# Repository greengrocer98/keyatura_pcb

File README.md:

# KEYATURA
Keyatura (/ˌkeɪ.əˈtʊə.rə/) - 36-key ergonomic keyboard with MX-spacing and support of choc_v2v1/MX switches.

### Features
* Promicro compatible MCU
* Hotswap for choc/MX
* Three led indicators
* Mill-Max hotswap sockets for MCU
* Power switch
* Reset button
### PCB
#### <div align="center">Top<div>

#### <div align="center">Bottom<div>

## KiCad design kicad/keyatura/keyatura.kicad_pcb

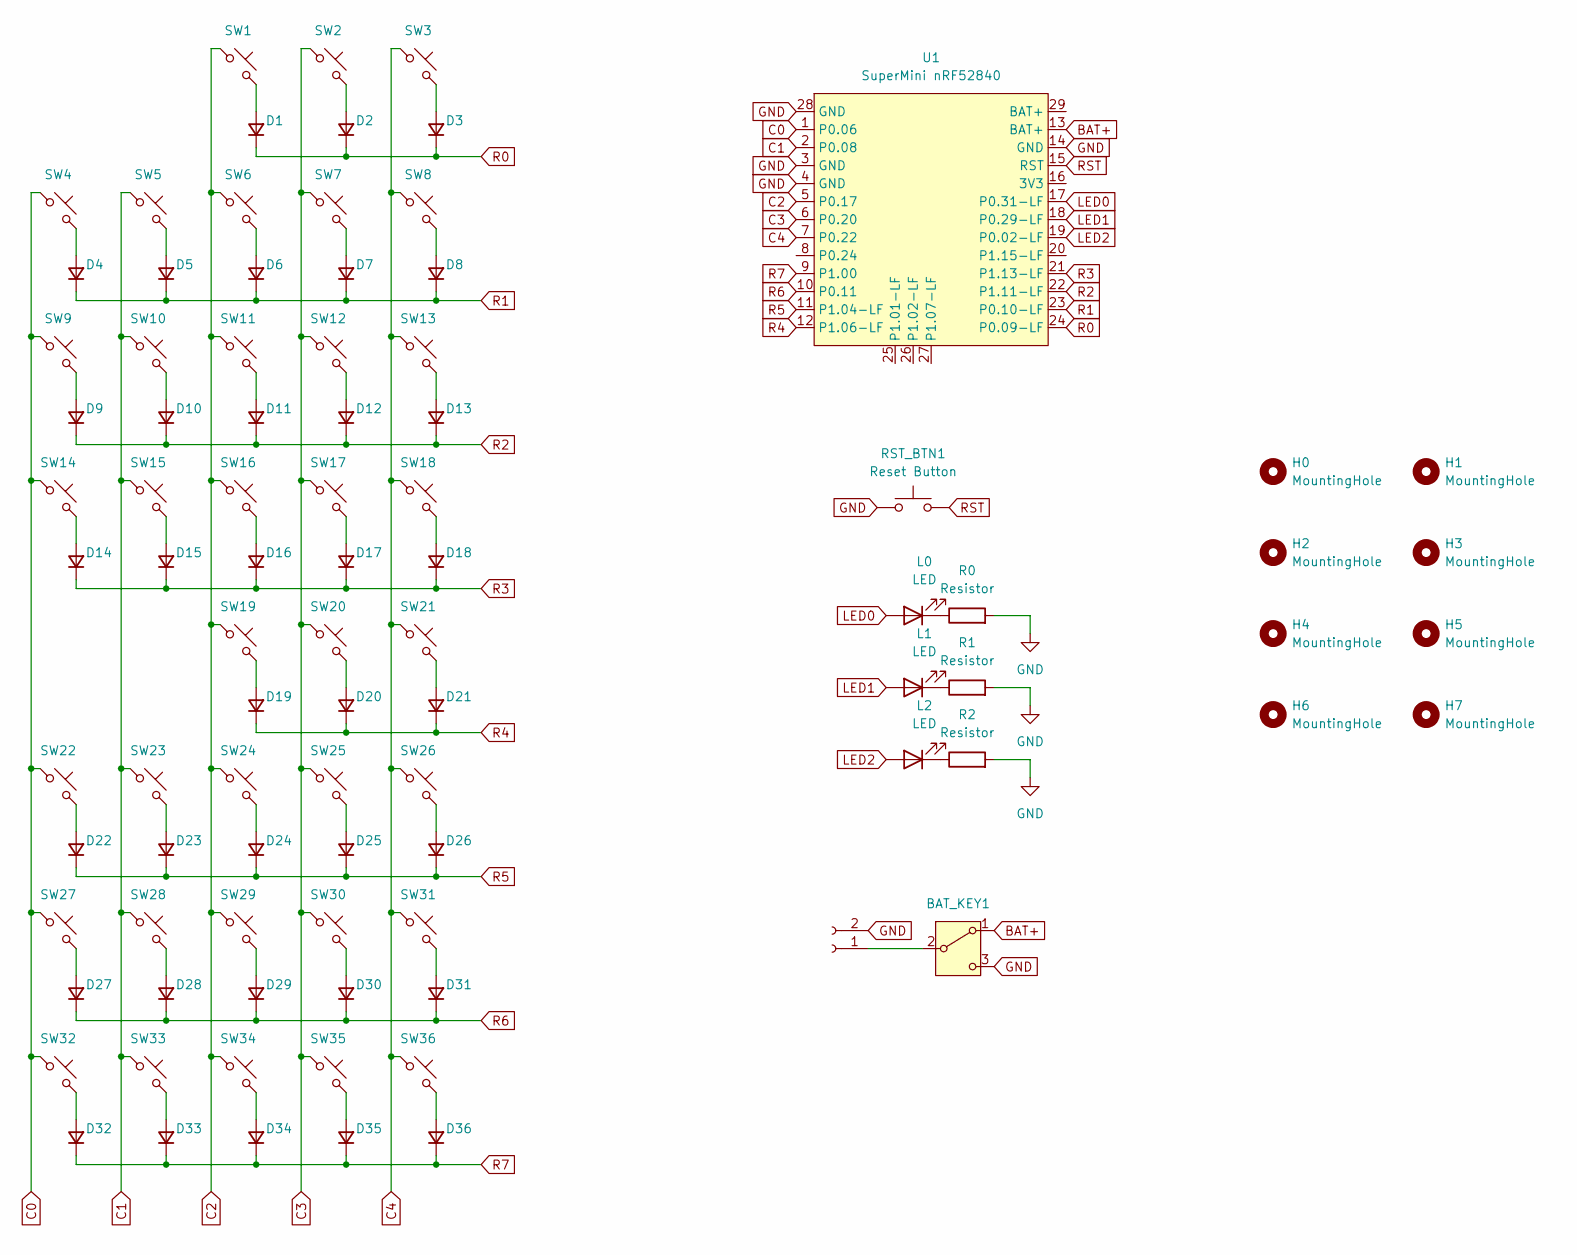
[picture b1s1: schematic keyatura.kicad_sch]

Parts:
BAT_KEY1: SW_SPDT; MSK-12C02
D1, D2, D3, D4, D5, D6, D7, D8, D9, D10, D11, D12, D13, D14, D15, D16, D17, D18, D19, D20, D21, D22, D23, D24, D25, D26, D27, D28, D29, D30, D31, D32, D33, D34, D35, D36: D; diode
H0, H1, H2, H3, H4, H5, H6, H7: MountingHole; mounting hole
J1: Battery; battery
L0, L1, L2: LED
R0, R1, R2: Resistor; resistor
RST_BTN1: Reset Button; reset button
SW1, SW2, SW3, SW4, SW5, SW6, SW7, SW8, SW9, SW10, SW11, SW12, SW13, SW14, SW15, SW16, SW17, SW18, SW19, SW20, SW21, SW22, SW23, SW24, SW25, SW26, SW27, SW28, SW29, SW30, SW31, SW32, SW33, SW34, SW35, SW36: SW_Push; SW_MX_Kailh_Choc_V1V2_HotSwap_Hybrid
U1: SuperMini nRF52840; supermini

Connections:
BAT+: BAT_KEY1.1 (A), U1.13 (BAT+)
C0: SW4.1, SW9.1, SW14.1, SW22.1, SW27.1, SW32.1, U1.1 (P0.06)
C1: SW5.1, SW10.1, SW15.1, SW23.1, SW28.1, SW33.1, U1.2 (P0.08)
C2: SW1.1, SW6.1, SW11.1, SW16.1, SW19.1, SW24.1, SW29.1, SW34.1, U1.5 (P0.17)
C3: SW2.1, SW7.1, SW12.1, SW17.1, SW20.1, SW25.1, SW30.1, SW35.1, U1.6 (P0.20)
C4: SW3.1, SW8.1, SW13.1, SW18.1, SW21.1, SW26.1, SW31.1, SW36.1, U1.7 (P0.22)
GND: BAT_KEY1.3 (C), J1.2, R0.2, R1.2, R2.2, RST_BTN1.1, U1.3 (GND), U1.4 (GND), U1.14 (GND), U1.28 (GND)
LED0: L0.2 (A), U1.17 (P0.31-LF)
LED1: L1.2 (A), U1.18 (P0.29-LF)
LED2: L2.2 (A), U1.19 (P0.02-LF)
unnamed: BAT_KEY1.2 (B), J1.1
unnamed: D1.2 (A), SW1.2
unnamed: D2.2 (A), SW2.2
unnamed: D3.2 (A), SW3.2
unnamed: D4.2 (A), SW4.2
unnamed: D5.2 (A), SW5.2
unnamed: D6.2 (A), SW6.2
unnamed: D7.2 (A), SW7.2
unnamed: D8.2 (A), SW8.2
unnamed: D9.2 (A), SW9.2
unnamed: D10.2 (A), SW10.2
unnamed: D11.2 (A), SW11.2
unnamed: D12.2 (A), SW12.2
unnamed: D13.2 (A), SW13.2
unnamed: D14.2 (A), SW14.2
unnamed: D15.2 (A), SW15.2
unnamed: D16.2 (A), SW16.2
unnamed: D17.2 (A), SW17.2
unnamed: D18.2 (A), SW18.2
unnamed: D19.2 (A), SW19.2
unnamed: D20.2 (A), SW20.2
unnamed: D21.2 (A), SW21.2
unnamed: D22.2 (A), SW22.2
unnamed: D23.2 (A), SW23.2
unnamed: D24.2 (A), SW24.2
unnamed: D25.2 (A), SW25.2
unnamed: D26.2 (A), SW26.2
unnamed: D27.2 (A), SW27.2
unnamed: D28.2 (A), SW28.2
unnamed: D29.2 (A), SW29.2
unnamed: D30.2 (A), SW30.2
unnamed: D31.2 (A), SW31.2
unnamed: D32.2 (A), SW32.2
unnamed: D33.2 (A), SW33.2
unnamed: D34.2 (A), SW34.2
unnamed: D35.2 (A), SW35.2
unnamed: D36.2 (A), SW36.2
unnamed: L0.1 (K), R0.1
unnamed: L1.1 (K), R1.1
unnamed: L2.1 (K), R2.1
R0: D1.1 (K), D2.1 (K), D3.1 (K), U1.24 (P0.09-LF)
R1: D4.1 (K), D5.1 (K), D6.1 (K), D7.1 (K), D8.1 (K), U1.23 (P0.10-LF)
R2: D9.1 (K), D10.1 (K), D11.1 (K), D12.1 (K), D13.1 (K), U1.22 (P1.11-LF)
R3: D14.1 (K), D15.1 (K), D16.1 (K), D17.1 (K), D18.1 (K), U1.21 (P1.13-LF)
R4: D19.1 (K), D20.1 (K), D21.1 (K), U1.12 (P1.06-LF)
R5: D22.1 (K), D23.1 (K), D24.1 (K), D25.1 (K), D26.1 (K), U1.11 (P1.04-LF)
R6: D27.1 (K), D28.1 (K), D29.1 (K), D30.1 (K), D31.1 (K), U1.10 (P0.11)
R7: D32.1 (K), D33.1 (K), D34.1 (K), D35.1 (K), D36.1 (K), U1.9 (P1.00)
RST: RST_BTN1.2, U1.15 (RST)

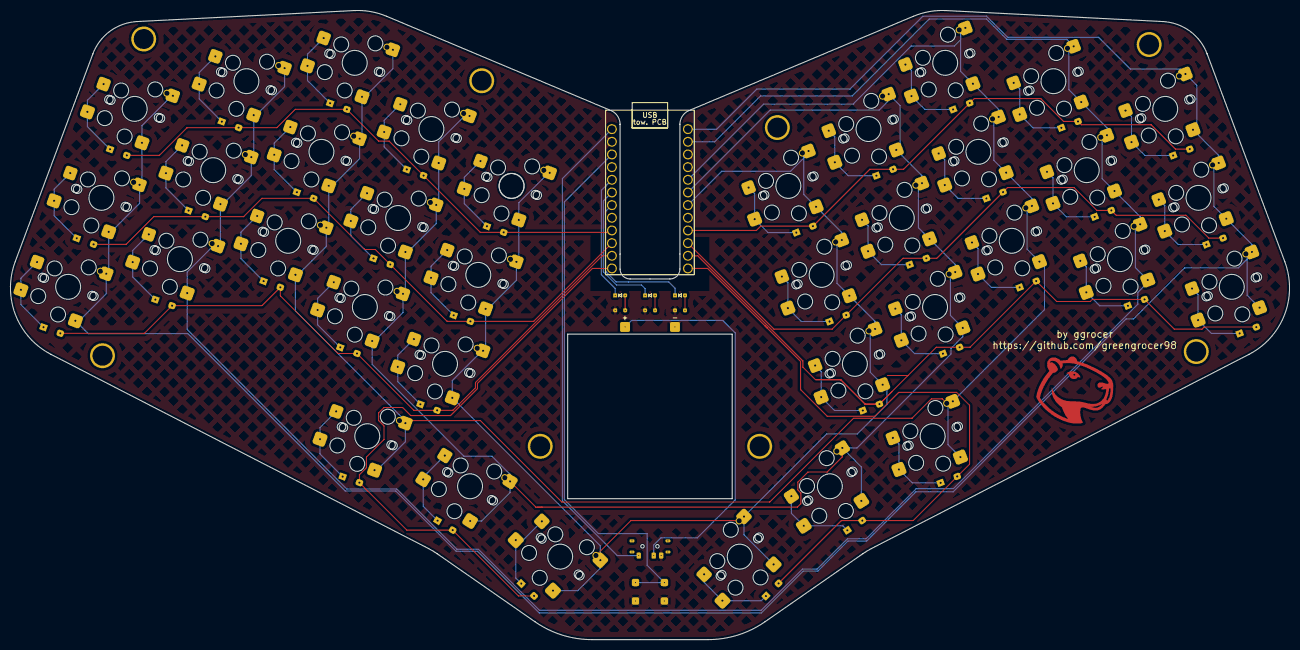
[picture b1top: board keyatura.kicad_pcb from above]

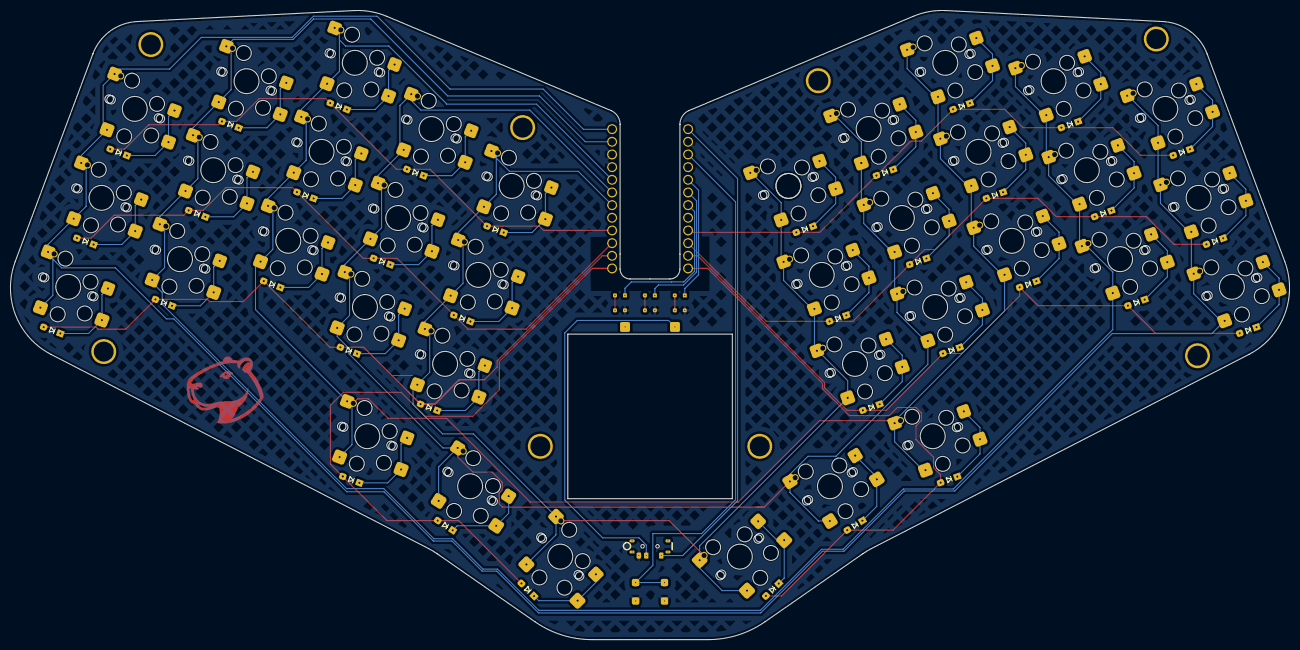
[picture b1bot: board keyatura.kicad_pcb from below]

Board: 2 copper layers, 256.5 x 126.2 mm, 90 parts (37 on the bottom side), 59 nets.

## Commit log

2025-08-06 initial work
2025-08-06 v0.1
2025-08-06 update footprint git modules
2025-08-07 added gerber files
2025-08-11 final changes in pcb before release
2025-08-11 updates in README
2025-08-26 fix diode footprints and outline edge cuts
2025-09-05 added 3d files and updated README
